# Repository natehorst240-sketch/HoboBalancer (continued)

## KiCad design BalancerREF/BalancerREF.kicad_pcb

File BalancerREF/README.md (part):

# BalancerREF (HOBOVibe) — reference rotor-vibration puck

ESP32-S3 firmware is in [firmware/README.md](firmware/README.md), including build/flash instructions, MR-VERT/TR-VERT controls, BLE/USB protocol, and a MicroVib comparison logger. Its measurement accuracy remains subject to bench validation.

Open **BalancerREF.kicad_pro**, then **BalancerREF.kicad_sch**, in KiCad 10.0.3 or later (KiCad 10 format; KiCad 9 will not open it). One A2 schematic sheet, Rev G (2026-09-19), hand-laid-out in KiCad (title "HOBOVibe Hobby Helicopter Dynamic Balancer"). The PCB is 50 x 50 mm, four layers (In1 GND plane, In2 +3V3 plane), fully routed with both inner planes uncut (the power nets that had crossed the +3V3 plane were moved to the outer layers on 2026-09-18). The custom library and project library table travel with the schematic. Most symbols are standard KiCad 10 symbols; IIS3DWB, SN74LVC1G123, LM1815, TS3021 and BQ24075RGT have local definitions with pin mappings verified against the manufacturer tables (see DATASHEET-VERIFICATION.md). The embedded USB-C receptacle and potentiometer symbols were re-synced from the KiCad 10 library (`scripts/sync_kicad10_symbols.py`) because KiCad 10 renamed the USB-C shield pin and footprint pad from S1 to SH; the pre-sync project is archived in `archives/RevB-before-kicad10-symbol-sync-20260907-214948.zip`.

This is a reference/troubleshooting instrument for approximate RPM, 1/rev vibration magnitude, phase, stability and trends. Maintenance balancing remains with calibrated MicroVib/DynaVibe equipment. Firmware and physical performance have not been validated by schematic ERC.

## Review files

- `review/BalancerREF.pdf`: searchable vector rendering of the one-sheet schematic.
- `review/erc.rpt`: KiCad 10 ERC report, all severities included.
- `review/connectivity-check.txt`: independent exact-net comparison against the intended circuits.
- `review/IC-pin-audit.csv`: every IC physical pad, manufacturer function, resulting net and unused-pin explanation.
- `review/pin-net-connections.csv`: all component pin/net connections.
- `review/unused-pins.json`: reasons for every NC marker.
- `DATASHEET-VERIFICATION.md`: manufacturer sources, pinout decisions and calculations.

All local functional circuits use real wires. Labels carry signals between complete blocks. Test points stay beside their measured circuits. Ground symbols all represent the same common ground.

## Operating intent

| Profile | Tach input | IR emitter | Vibration |
|---|---|---|---|
| MR-VERT | External isolated two-wire VR pickup at J3 / J_MAG | Off | Internal IIS3DWB on SPI, all axes available |
| TR-VERT | Onboard pulsed-red synchronous-detection optical tach (retroreflective tape) | 20 kHz pulses | Same sensor |

### Rev G changes (2026-09-19)

Three corrections from a Reddit review of the Rev C sheet, all of which still applied
to Rev F. `scripts/rev_g_usb_esd_tvs_u9.py` edits the schematic and
`scripts/sync_board_rev_g.py` carries the result into the board.

- **D3 was backwards.** The SMF5.0A is a unidirectional TVS, and DATASHEET-VERIFICATION.md
  had recorded it as bidirectional with "either orientation valid". It was drawn cathode
  to GND, anode to VBUS: forward biased, so it would have clamped USB VBUS at a diode
  drop as soon as a cable went in. Cathode (pin 1) is now on USB_VBUS and the board
  footprint is rotated 180 to match.
- **USB data lines now go through U7.** The SRV05-4's pins 4 and 6 were marked NC, so
  D+/D- reached the array as stubs. Pin 6 is directly across from pin 1 and pin 4 across
  from pin 3, so the drawing now takes D- in at pin 1 and out at pin 6, D+ in at pin 3
  and out at pin 4, and the pads on the board carry those nets. The SRV05-4 has no
  internal path between its I/O pins, so both ends of each pair keep the same net name
  and the trace itself makes the through-connection: `scripts/route_rev_g.py` runs a
  0.2 mm track straight across the package from pin 3 to pin 4 and from pin 1 to pin 6.
- **U9 pin 1 no longer floats when the head is unplugged.** OPT_COMP arrives from the
  optical head through J5 pin 5 (driven via R32 on the head). In MR-VERT the head is
  normally not connected, leaving a CMOS input open. R39 100k to GND holds it low; it is
  placed on the back directly under the OPT_COMP trace just left of U9, so one via at each
  pad connects it. U9 pin 2 (via R29 from OPT_LED_EN) floats
  only during ESP32 reset, when the GPIO is still an input, and was left alone.
- `review/reddit/` re-rendered from the Rev G sheet at higher resolution (the old set
  was Rev C at roughly 200 DPI; see `scripts/render_review_images.py`).

### Rev F changes (2026-09-13)

Rev F is the **repo-review revision**: no new function, but several things that had to
be right before any copper is routed. Every claim was checked against the manufacturer
source, and two of them did not survive that check (see DATASHEET-VERIFICATION.md for
the full record, including what was deliberately NOT changed).

- **PD1 polarity corrected - the optical tach could never have worked.** The detector
  was wired cathode to +3V3 and anode to the transimpedance summing node. Reverse bias
  is correct that way, which is why it survived this long, but photocurrent leaves the
  ANODE, so it was injected into the summing node instead of pulled out of it. The
  inverting TIA then drove TIA_OUT down, the inverting second stage drove OPT_AMP UP
  from its 1.65 V idle, and U4 has OPT_AMP on IN- against a 1.016 V threshold on IN+.
  The comparator input sat 634 mV above the threshold and light pushed it further away,
  so the output never left its low state and TR-VERT had no tach at all. Cathode now
  goes to PD_TIA_IN and the anode to GND: same 1.65 V reverse bias, but TIA_OUT rises,
  OPT_AMP falls through the threshold, and the 470k hysteresis works as drawn. About
  5.3 uA of photocurrent trips it. Bonus: the emitter turn-off edge, which lands inside
  the gate window and cannot be rejected, now couples into the summing node in the
  non-detection direction - which matters because this revision also moved Q1 nearer
  PD1.
- **R18 3.0 -> 3.9 ohm on the head board.** The emitter runs from SYS_SW, and the
  BQ24075 regulates OUT to 5.5 V, so the old value gave about 1.1 A peak into D1's 1 A
  absolute maximum. The BOM note had only checked the 4.2 V battery case. This is a
  regression introduced by Rev E: the Schottky it removed had been holding SYS near
  4.55 V. 3.9 ohm keeps the 500 mA design point at a full cell and lands at about
  0.90 A worst case.
- **U9 SN74LVC1G08 -> SN74LVC1G132.** R29/C26 fed the AND gate a 0.47 us edge against a
  10 ns/V input transition spec. The 1G132 is a Schmitt NAND on the identical SOT-23-5
  pinout, so the footprint is untouched, and it conditions both inputs rather than only
  the RC branch. It inverts, so U10's trigger moved from B rising to ~A falling - the
  SN74LVC1G123 supports both edges.
- **Switching loop off the vias.** L1 and C4-C7 were on the back with U6 on the front,
  so a 2.4 MHz switching node and both its input and output caps reached the IC through
  vias. They moved to U6's face, and C1/C2/C3/C30 followed for the BQ24075. The
  "ICs front, passives back" rule does not survive contact with a switching converter.
  Two follow-on corrections came out of review: aim at the **pin**, not the net, and
  place the fastest part first. U6 pins 5-8 are all on SYS_SW, so targeting "the input
  net" had put the caps next to EN and PS/SYNC - logic inputs that happen to be strapped
  high - rather than VIN and VINA; and the 10u bulk had taken the close spot while the
  100n sat 4.4 mm out. C5 now sits 2.07 mm from VINA and C4 2.68 mm from VIN. C1, the
  100n bypass on the BQ24075's IN pin, turned out to be **24 mm away on the back of the
  board**, which is the same as not fitting it; it is now 5.3 mm out on the front.
  TP6 and TP10 were squatting immediately left of U6 - the side VIN and PGND are on -
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
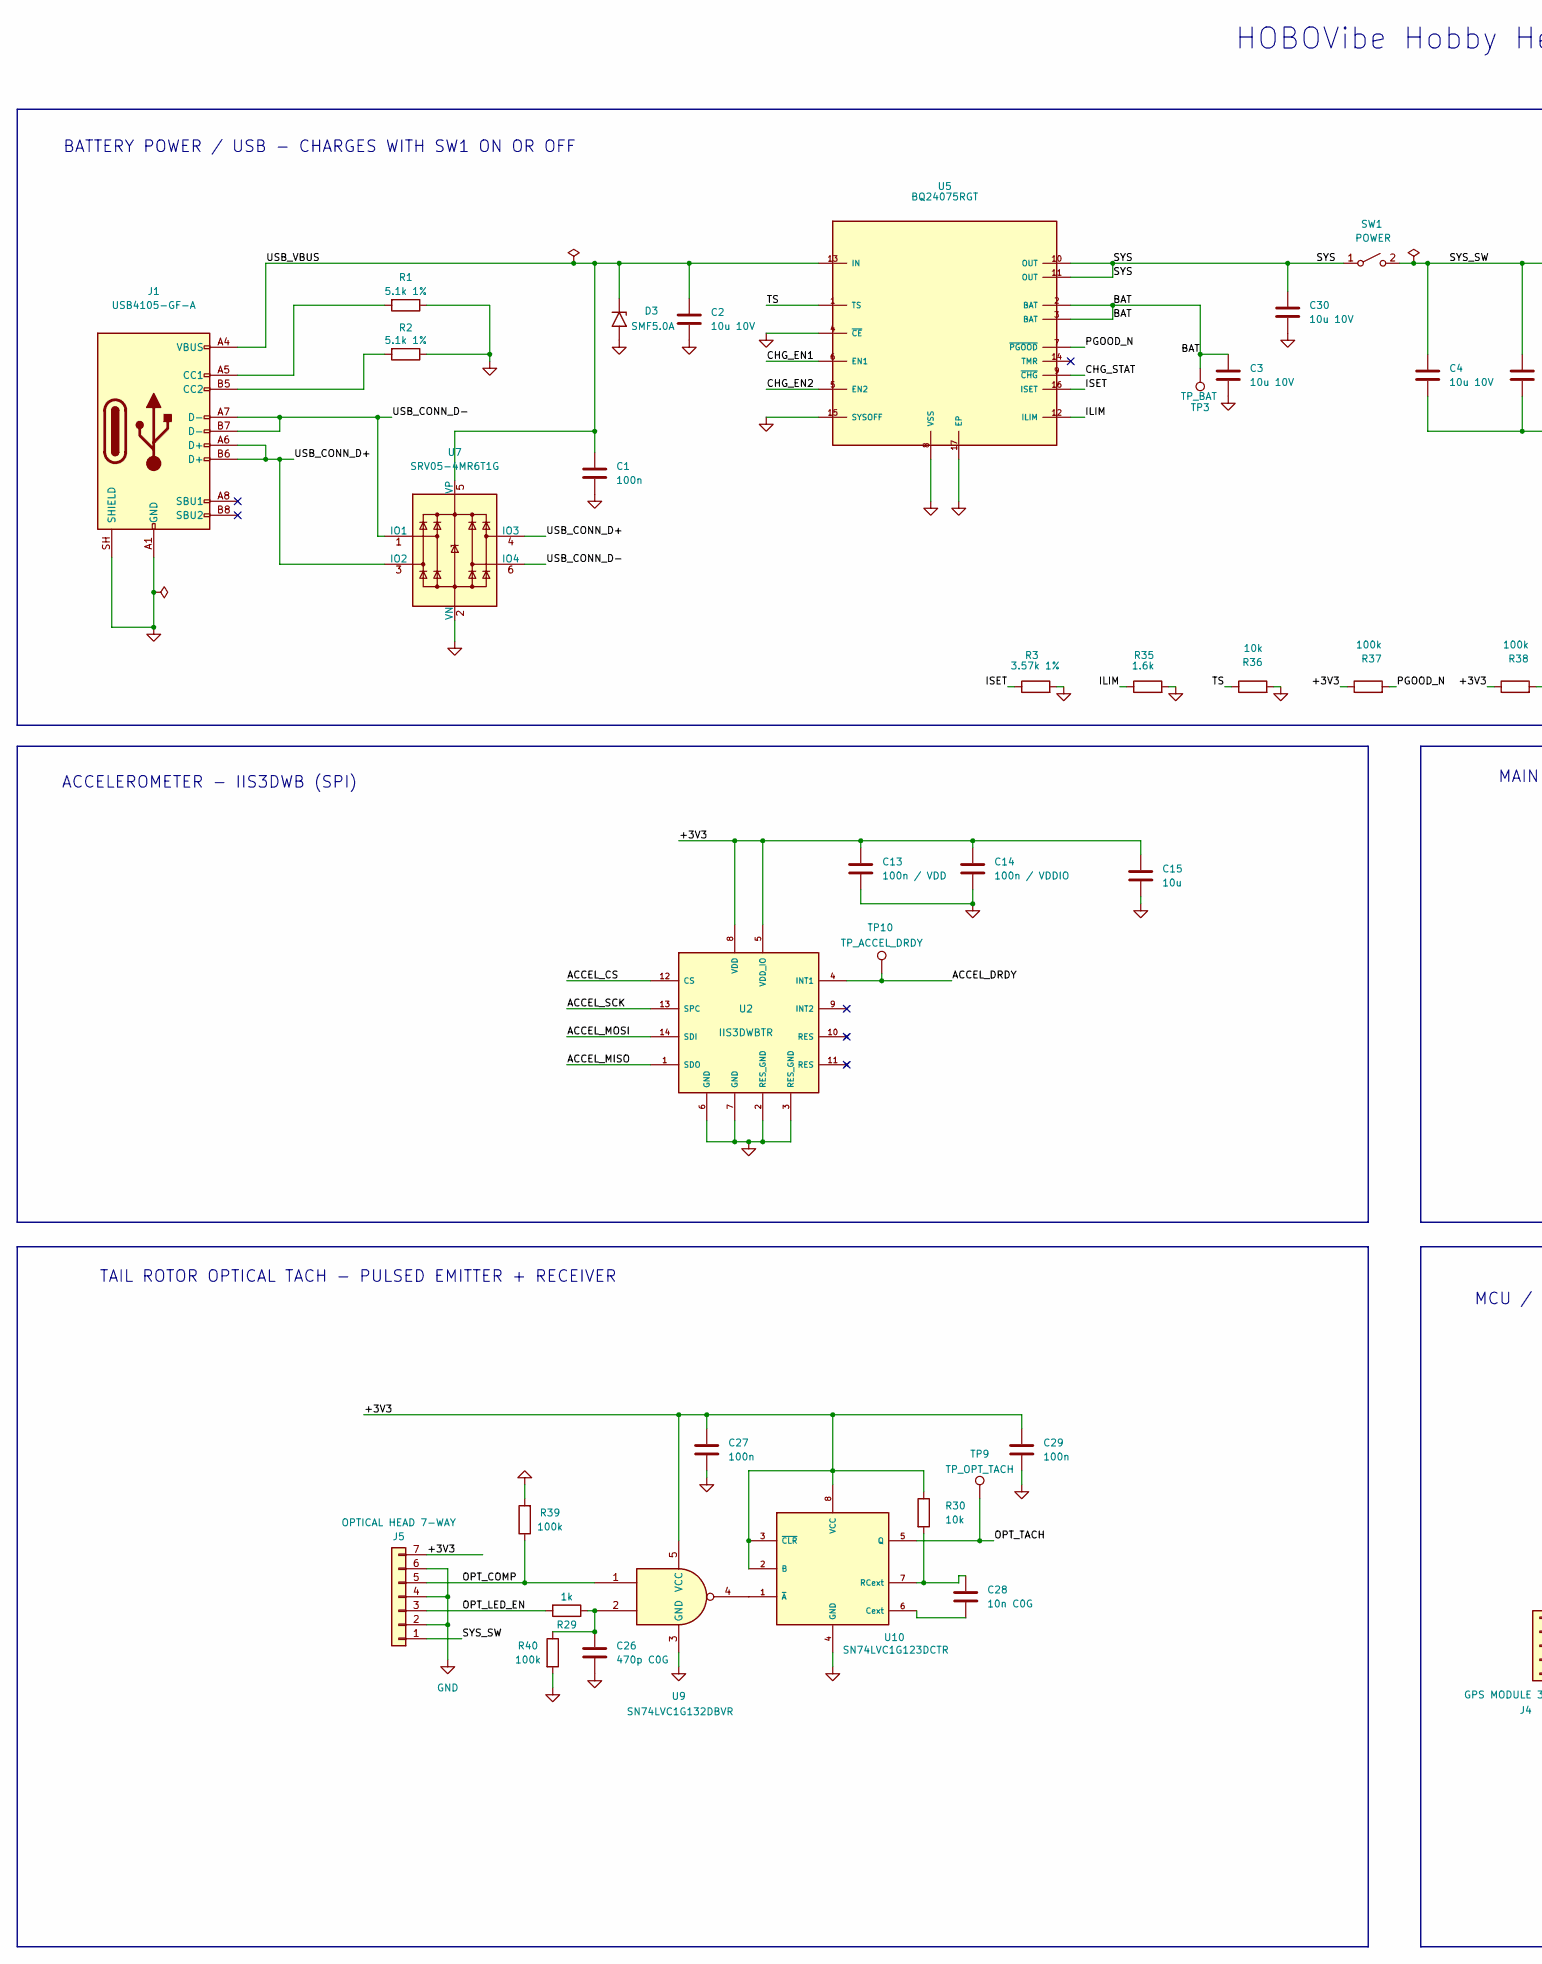
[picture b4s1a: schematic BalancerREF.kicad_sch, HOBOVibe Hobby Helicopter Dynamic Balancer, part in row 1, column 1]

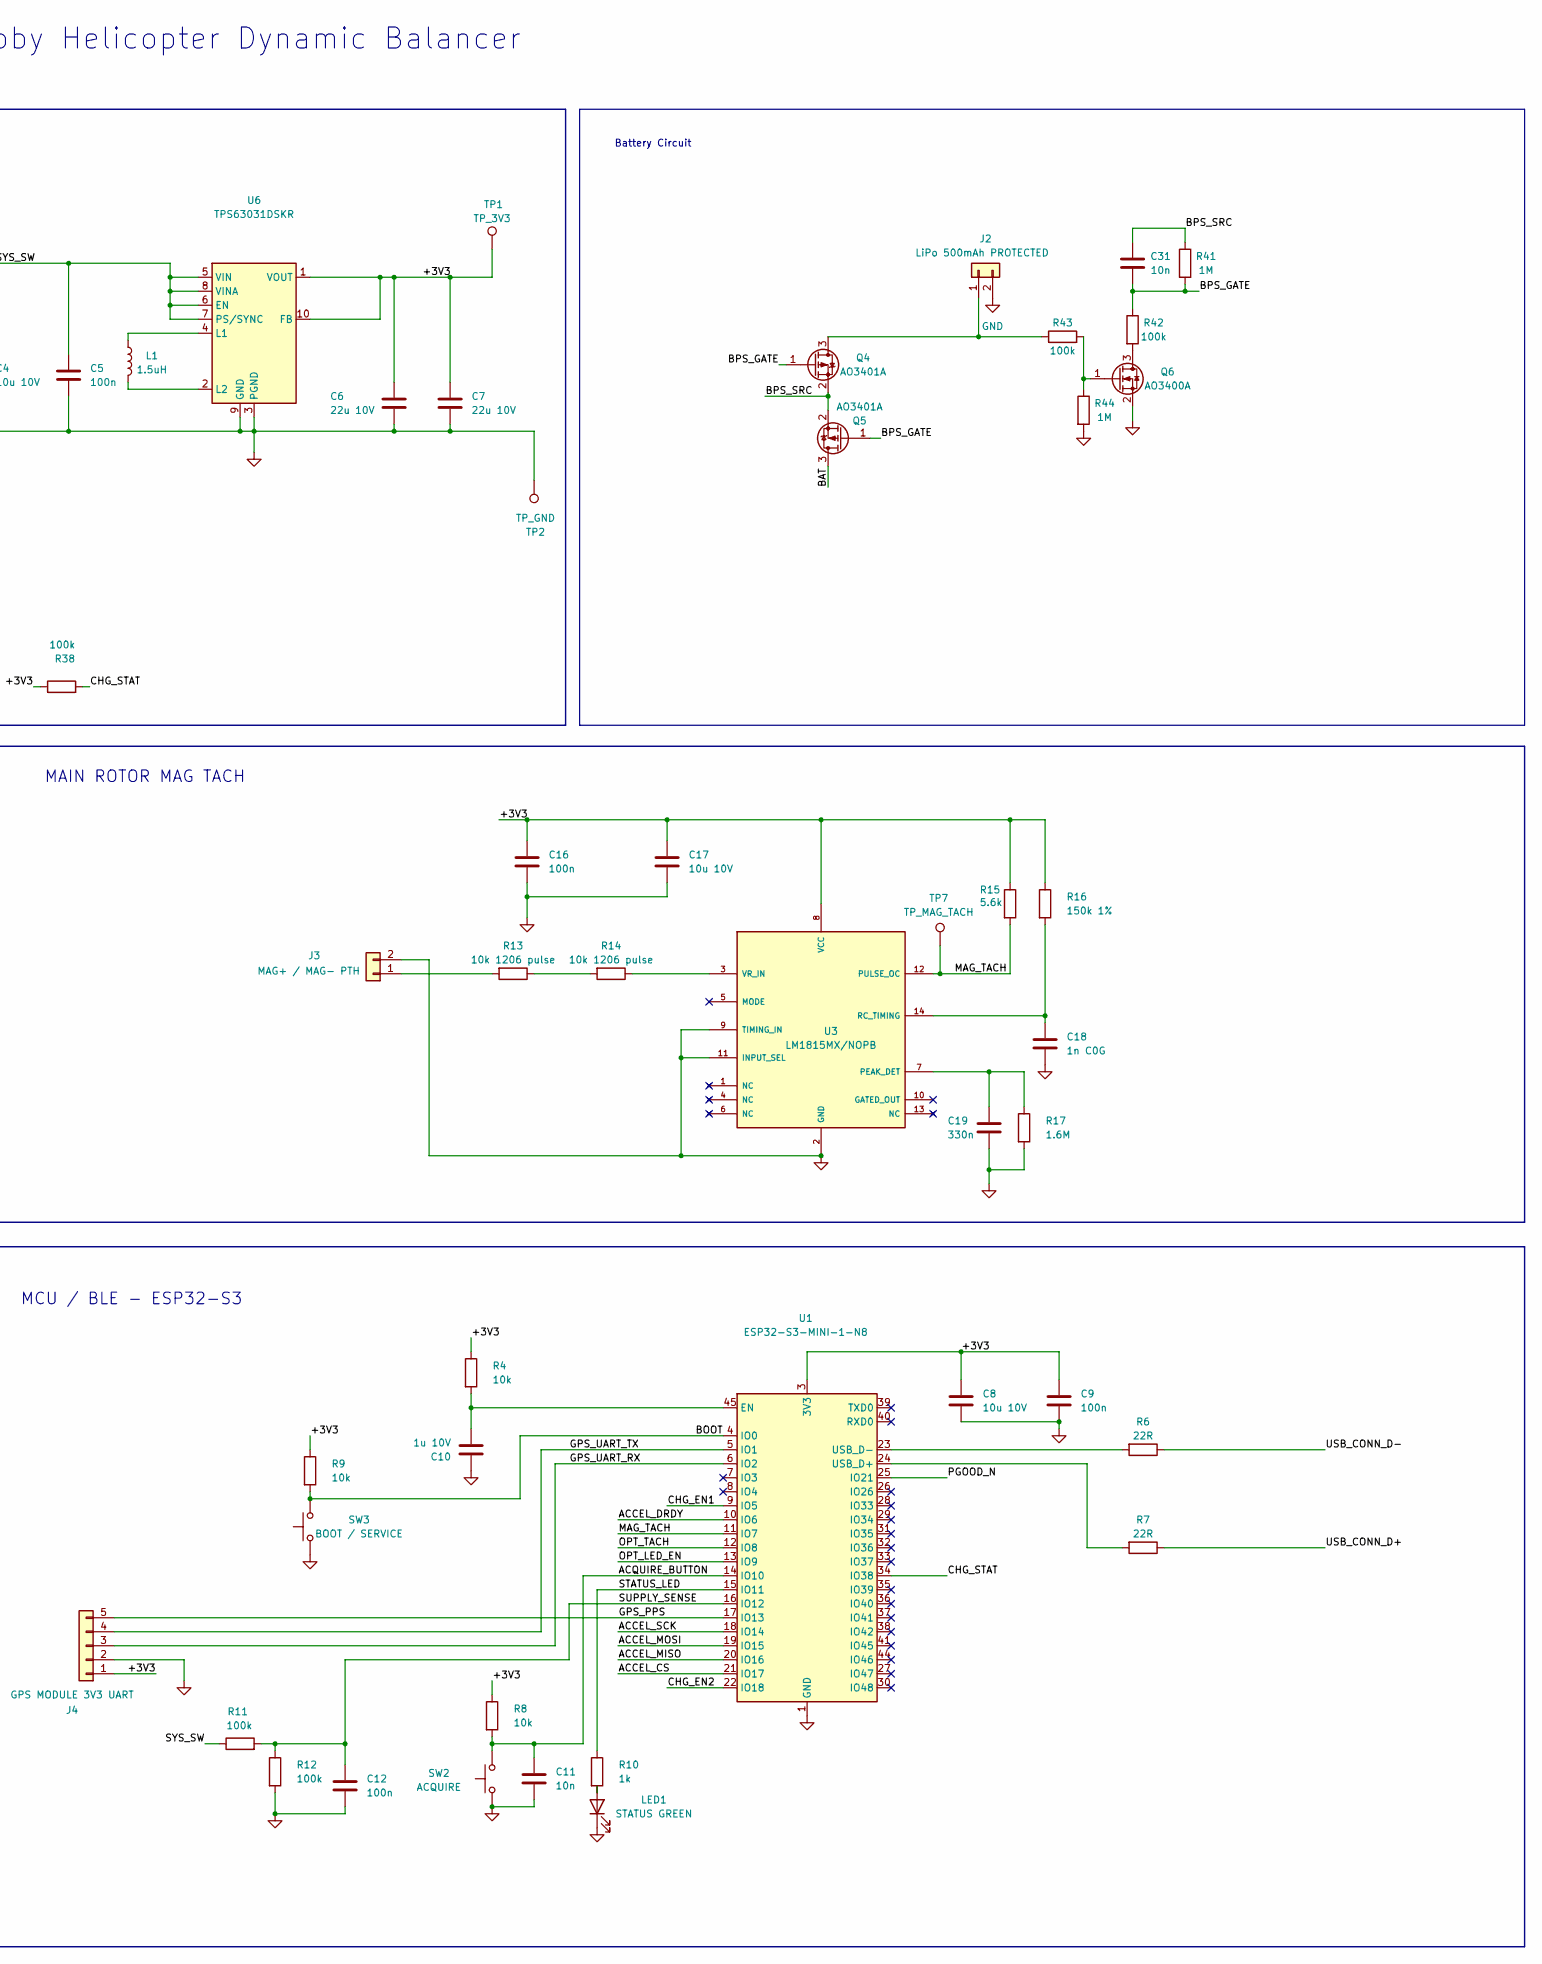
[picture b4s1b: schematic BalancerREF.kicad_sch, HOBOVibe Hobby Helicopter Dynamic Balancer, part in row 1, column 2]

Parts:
C1, C5, C9: 100n; C_0805_2012Metric; MPN 100n / 10V
C2, C3, C4, C8: 10u 10V; C_0805_2012Metric; MPN 10u / 10V X7R
C6, C7: 22u 10V; C_0805_2012Metric; MPN 22u / 10V X7R
C10: 1u 10V; C_0805_2012Metric; MPN 1u / 10V
C11, C31: 10n; C_0805_2012Metric; MPN 10n
C12, C16, C27, C29: 100n; C_0805_2012Metric; MPN 100n
C13: 100n / VDD; C_0805_2012Metric; MPN 100n / VDD
C14: 100n / VDDIO; C_0805_2012Metric; MPN 100n / VDDIO
C15: 10u; C_0805_2012Metric; MPN 10u
C17: 10u 10V; C_0805_2012Metric; MPN 10u / 10V
C18: 1n C0G; C_0805_2012Metric; MPN 1n C0G
C19: 330n; C_0805_2012Metric; MPN 330n
C26: 470p C0G; C_0805_2012Metric; MPN 470p C0G
C28: 10n C0G; C_0805_2012Metric; MPN 1n C0G
C30: 10u 10V; C_0805_2012Metric; MPN 10u 10V
D3: SMF5.0A; D_SMF; MPN SMF5.0A
J1: USB4105-GF-A; USB_C_Receptacle_GCT_USB4105-xx-A_16P_TopMnt_Horizontal; MPN USB4105-GF-A
J2: LiPo 500mAh PROTECTED; JST_PH_B2B-PH-K_1x02_P2.00mm_Vertical; MPN JST B2B-PH-K-S
J3: MAG+ / MAG- PTH; SolderWire-0.1sqmm_1x02_P3.6mm_D0.4mm_OD1mm; MPN MAG+ / MAG- PTH
J4: GPS MODULE 3V3 UART; PinHeader_1x05_P2.54mm_Vertical; MPN PinHeader 1x05 2.54mm
J5: OPTICAL HEAD 7-WAY; JST_GH_SM07B-GHS-TB_1x07-1MP_P1.25mm_Horizontal; MPN SM07B-GHS-TB
L1: 1.5uH; L_Murata_DFE201610P; MPN DFE201612PD-1R5M=P2
LED1: STATUS GREEN; LED_0603_1608Metric; MPN STATUS GREEN
Q4, Q5: AO3401A; SOT-23; MPN AO3401A
Q6: AO3400A; SOT-23; MPN AO3400A
R1, R2: 5.1k 1%; R_0603_1608Metric; MPN 5.1k 1%
R3: 3.57k 1%; R_0603_1608Metric; MPN 3.57k 1%
R4, R8, R9, R36: 10k; R_0603_1608Metric; MPN 10k
R6, R7: 22R; R_0603_1608Metric; MPN 22R
R10, R29: 1k; R_0603_1608Metric; MPN 1k
R11, R12, R37, R38, R39, R40, R42, R43: 100k; R_0603_1608Metric; MPN 100k
R13, R14: 10k 1206 pulse; R_1206_3216Metric; MPN 10k 1206 pulse
R15: 5.6k; R_0603_1608Metric; MPN 5.6k
R16: 150k 1%; R_0603_1608Metric; MPN 150k 1%
R17: 1.6M; R_0603_1608Metric; MPN 1.6M
R30: 10k; R_0603_1608Metric; MPN 100k
R35: 1.6k; R_0603_1608Metric; MPN 1.6k
R41, R44: 1M; R_0603_1608Metric; MPN 1M
SW1: POWER; SW_Slide-03_Wuerth-WS-SLTV_10x2.5x6.4_P2.54mm; MPN POWER
SW2: ACQUIRE; SW_PUSH_6mm; MPN ACQUIRE
SW3: BOOT / SERVICE; SW_PUSH_6mm; MPN BOOT / SERVICE
TP1: TP_3V3; TestPoint_Pad_D1.0mm; MPN TP_3V3
TP2: TP_GND; TestPoint_Pad_D1.0mm; MPN TP_GND
TP3: TP_BAT; TestPoint_Pad_D1.0mm; MPN TP_BAT
TP7: TP_MAG_TACH; TestPoint_Pad_D1.0mm; MPN TP_MAG_TACH
TP9: TP_OPT_TACH; TestPoint_Pad_D1.0mm; MPN TP_OPT_TACH
TP10: TP_ACCEL_DRDY; TestPoint_Pad_D1.0mm; MPN TP_ACCEL_DRDY
U1: ESP32-S3-MINI-1-N8; ESP32-S2-MINI-1; MPN ESP32-S3-MINI-1-N8
U2: IIS3DWBTR; LGA-14_3x2.5mm_P0.5mm_LayoutBorder3x4y; MPN IIS3DWBTR
U3: LM1815MX/NOPB; SOIC-14_3.9x8.7mm_P1.27mm; MPN LM1815MX/NOPB
U5: BQ24075RGT; QFN-16-1EP_3x3mm_P0.5mm_EP1.675x1.675mm; MPN BQ24075RGTR
U6: TPS63031DSKR; WSON-10-1EP_2.5x2.5mm_P0.5mm_EP1.2x2mm; MPN TPS63031DSKR
U7: SRV05-4MR6T1G; SOT-23-6; MPN SRV05-4MR6T1G
U9: SN74LVC1G132DBVR; SOT-23-5; MPN SN74LVC1G132DBVR
U10: SN74LVC1G123DCTR; SSOP-8_2.95x2.8mm_P0.65mm; MPN SN74LVC1G123DCTR

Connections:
/+3V3: C6.1, C7.1, C8.1, C9.1, C13.1, C14.1, C15.1, C16.1, C17.1, C27.1, C29.1, J4.1, J5.7, R4.1, R8.1, R9.1, R15.1, R16.1, R30.1, R37.1, R38.1, TP1.1 (1_1), U1.3 (3V3), U2.5 (VDD_IO), U2.8 (VDD), U3.8 (VCC), U6.1 (VOUT), U6.10 (FB), U9.5 (VCC), U10.2 (B), U10.3 (~CLR), U10.8 (VCC)
/ACCEL_CS: U1.21 (IO17), U2.12 (CS)
/ACCEL_DRDY: TP10.1 (1_1), U1.10 (IO6), U2.4 (INT1)
/ACCEL_MISO: U1.20 (IO16), U2.1 (SDO)
/ACCEL_MOSI: U1.19 (IO15), U2.14 (SDI)
/ACCEL_SCK: U1.18 (IO14), U2.13 (SPC)
/ACQUIRE_BUTTON: C11.1, R8.2, SW2.2, U1.14 (IO10)
/BAT: C3.1, Q5.3 (D), TP3.1 (1_1), U5.2 (BAT), U5.3 (BAT)
/BOOT: R9.2, SW3.2, U1.4 (IO0)
/BPS_GATE: C31.2, Q4.1 (G), Q5.1 (G), R41.2, R42.1
/BPS_SRC: C31.1, Q4.2 (S), Q5.2 (S), R41.1
/CHG_EN1: U1.9 (IO5), U5.6 (EN1)
/CHG_EN2: U1.22 (IO18), U5.5 (EN2)
/CHG_STAT: R38.2, U1.34 (IO38), U5.9 (~CHG)
/GPS_PPS: J4.5, U1.17 (IO13)
/GPS_UART_RX: J4.3, U1.6 (IO2)
/GPS_UART_TX: J4.4, U1.5 (IO1)
/ILIM: R35.1, U5.12 (ILIM)
/ISET: R3.1, U5.16 (ISET)
/MAG_TACH: R15.2, TP7.1 (1_1), U1.11 (IO7), U3.12 (PULSE_OC)
/OPT_COMP: J5.5, R39.1, U9.1
/OPT_LED_EN: J5.3, R29.2, U1.13 (IO9)
/OPT_TACH: TP9.1 (1_1), U1.12 (IO8), U10.5 (Q)
/PGOOD_N: R37.2, U1.25 (IO21), U5.7 (~PGOOD)
/STATUS_LED: R10.1, U1.15 (IO11)
/SUPPLY_SENSE: C12.1, R11.2, R12.1, U1.16 (IO12)
/SYS: C30.1, SW1.1 (A), U5.10 (OUT), U5.11 (OUT)
/SYS_SW: C4.1, C5.1, J5.1, R11.1, SW1.2 (B), U6.5 (VIN), U6.6 (EN), U6.7 (PS/SYNC), U6.8 (VINA)
/TS: R36.1, U5.1 (TS)
/USB_CONN_D+: J1.A6 (D+), J1.B6 (D+), R7.1, U7.3 (IO2), U7.4 (IO3)
/USB_CONN_D-: J1.A7 (D-), J1.B7 (D-), R6.1, U7.1 (IO1), U7.6 (IO4)
/USB_VBUS: C1.1, C2.1, D3.1 (A1), J1.A4 (VBUS), J1.A9 (VBUS), J1.B4 (VBUS), J1.B9 (VBUS), U5.13 (IN), U7.5 (VP)
GND: C1.2, C2.2, C3.2, C4.2, C5.2, C6.2, C7.2, C8.2, C9.2, C10.2, C11.2, C12.2, C13.2, C14.2, C15.2, C16.2, C17.2, C18.2, C19.2, C26.2, C27.2, C29.2, C30.2, D3.2 (A2), J1.A1 (GND), J1.A12 (GND), J1.B1 (GND), J1.B12 (GND), J1.SH (SHIELD), J2.2, J3.2, J4.2, J5.2, J5.4, J5.6, LED1.1 (K), Q6.2 (S), R1.1, R2.1, R3.2, R12.2, R17.2, R35.2, R36.2, R39.2, R40.2, R44.2, SW2.1, SW3.1, TP2.1 (1_1), U1.1 (GND), U1.2 (GND), U1.42 (GND), U1.43 (GND), U1.46 (GND), U1.47 (GND), U1.48 (GND), U1.49 (GND), U1.50 (GND), U1.51 (GND), U1.52 (GND), U1.53 (GND), U1.54 (GND), U1.55 (GND), U1.56 (GND), U1.57 (GND), U1.58 (GND), U1.59 (GND), U1.60 (GND), U1.61 (GND), U1.62 (GND), U1.63 (GND), U1.64 (GND), U1.65 (GND), U2.2 (RES_GND), U2.3 (RES_GND), U2.6 (GND), U2.7 (GND), U3.2 (GND), U3.9 (TIMING_IN)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
unnamed: C26.1, R29.1, R40.1, U9.2
unnamed: J1.A5 (CC1), R1.2
unnamed: J1.B5 (CC2), R2.2
unnamed: J2.1, Q4.3 (D), R43.1
unnamed: J3.1, R13.2
unnamed: LED1.2 (A), R10.2
unnamed: Q6.3 (D), R42.2
unnamed: Q6.1 (G), R43.2, R44.1
unnamed: R13.1, R14.2
unnamed: C10.1, R4.2, U1.45 (EN)
unnamed: R7.2, U1.24 (USB_D+)
unnamed: R6.2, U1.23 (USB_D-)
unnamed: C19.1, R17.1, U3.7 (PEAK_DET)
unnamed: C18.1, R16.2, U3.14 (RC_TIMING)
unnamed: R14.1, U3.3 (VR_IN)
unnamed: L1.1, U6.4 (L1)
unnamed: L1.2, U6.2 (L2)
unnamed: C28.2, U10.6 (Cext)
unnamed: C28.1, R30.2, U10.7 (RCext)
unnamed: U9.4, U10.1 (~A)

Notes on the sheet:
Battery Circuit
BATTERY POWER / USB - CHARGES WITH SW1 ON OR OFF
MCU / BLE - ESP32-S3
HOBOVibe Hobby Helicopter Dynamic Balancer
ACCELEROMETER - IIS3DWB (SPI)
MAIN ROTOR MAG TACH
TAIL ROTOR OPTICAL TACH - PULSED EMITTER + RECEIVER

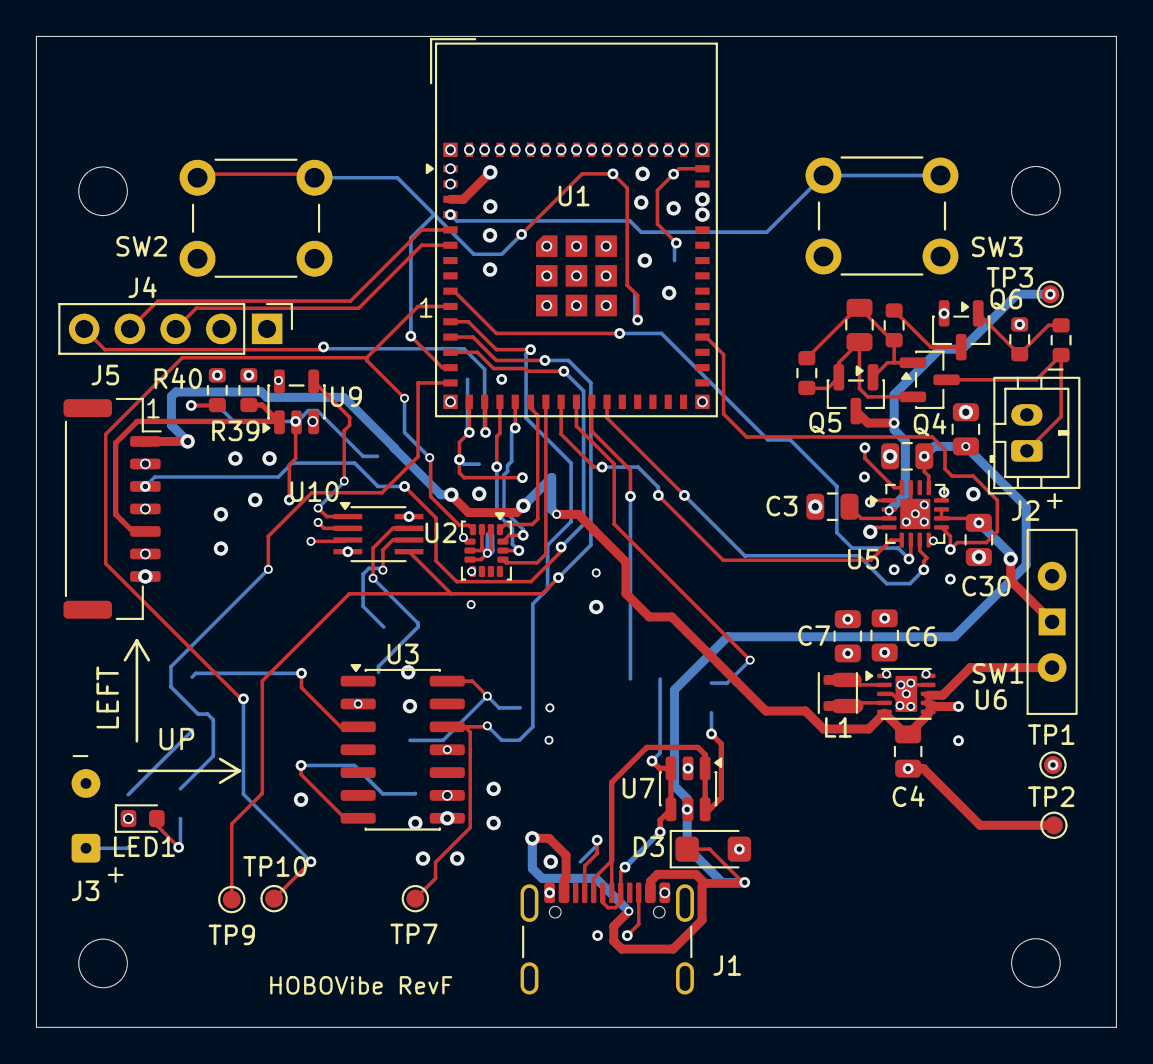
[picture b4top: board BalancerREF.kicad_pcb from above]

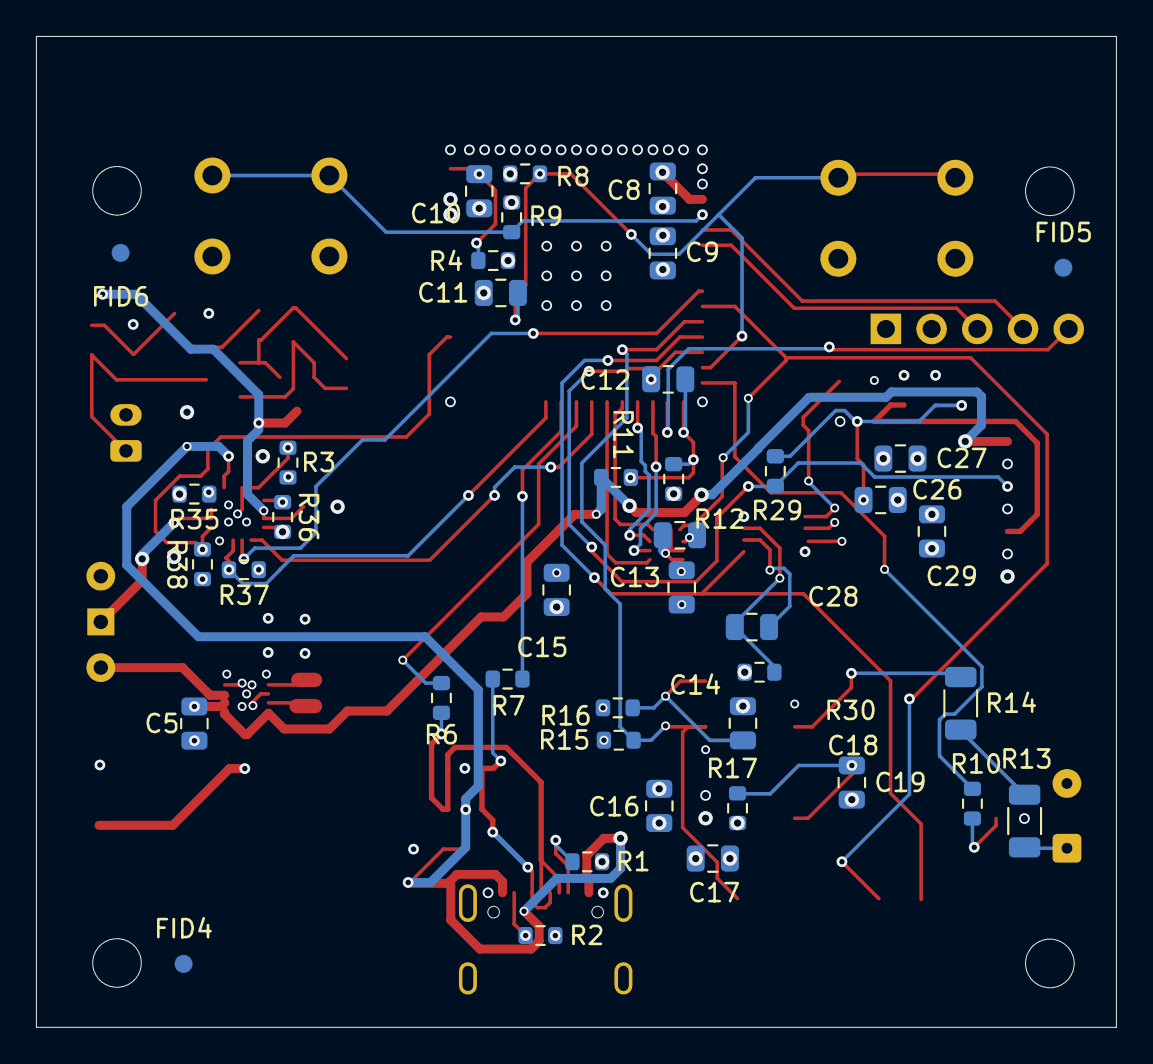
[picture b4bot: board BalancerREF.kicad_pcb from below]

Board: 4 copper layers, 60.0 x 55.0 mm, 88 parts (42 on the bottom side), 53 nets.

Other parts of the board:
FID4, FID5, FID6: FIDUCIAL; Fiducial_1mm_Mask2mm
H1, H2, H3, H4: M2.5 MOUNT; MountingHole_2.7mm_M2.5

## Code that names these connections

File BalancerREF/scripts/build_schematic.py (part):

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 rr=R('22R',368.3,yy,90);wire((358.14,yy),p(rr,2));route(rr,1,(401.32,yy));label(net,401.32,yy)
 tp(tpref,'TP_USB_D-' if n==23 else 'TP_USB_D+',388.62,yy-5.08,(388.62,yy))
# GPIO allocations deliberately avoid strapping pins and internal flash signals.
gpio={10:'ACCEL_DRDY',11:'MAG_TACH',12:'OPT_TACH',13:'OPT_LED_EN',14:'ACQUIRE_BUTTON',15:'STATUS_LED',16:'SUPPLY_SENSE',18:'ACCEL_SCK',19:'ACCEL_MOSI',20:'ACCEL_MISO',21:'ACCEL_CS'}
for pin,net in gpio.items():
 a=p('U1',pin);wire(a,(241.3,a[1]));label(net,241.3,a[1])
usedpins={3,45,4,23,24,*gpio.keys(),1,2,42,43,*range(46,66)}
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 wire((x,182.88),(x+20.32,182.88));label(net,x+20.32,182.88)
 if ref=='SW2':
  cc=C('10n',60.96,195.58);route(cc,1,(60.96,182.88));route(cc,2,(60.96,208.28),(40.64,208.28))
rs=R('1k',139.7,170.18);route(rs,1,(139.7,160.02));label('STATUS_LED',139.7,160.02)
place('LED1',('Device','LED'),139.7,190.5,90,'STATUS GREEN',fp='LED_SMD:LED_0603_1608Metric',field=(150,189.23));route(rs,2,p('LED1',2));route('LED1',1,(139.7,208.28));gnd(139.7,208.28)
# Switched supply divider: cannot back-power the MCU when SW1 is OFF.
rh=R('100k',35.56,233.68);rl=R('100k',68.58,241.3)
route(rh,1,(35.56,223.52));rail('SYS_SW',35.56,223.52)
route(rh,2,(35.56,236.22),(68.58,236.22),p(rl,1));route(rl,2,(68.58,251.46));gnd(68.58,251.46)
wire((68.58,236.22),(91.44,236.22));label('SUPPLY_SENSE',91.44,236.22)
ca=C('100n',81.28,243.84);route(ca,1,(81.28,236.22));route(ca,2,(81.28,251.46),(68.58,251.46))
text('Active-low buttons; debounce in firmware.\nBOOT held low during reset enters download.\nSupply ADC: SYS_SW / 2 with 100n at the pin; dead when OFF.\nOne green status LED; patterns set by firmware.',101.6,220.98,1.2)

# Accelerometer: IIS3DWB on 4-wire SPI. RES pads 2/3 to GND, 10/11 unconnected, INT1 = data-ready.
place('U2','IIS3DWBTR',99.06,325.12,field=(99.06,302.26),mpn='IIS3DWBTR')
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 a=p('U2',n);wire(a,(20.32,a[1]));label(net,20.32,a[1],180)
for n in [6,7,2,3]:route('U2',n,(p('U2',n)[0],350.52))
wire((91.44,350.52),(106.68,350.52));gnd(99.06,350.52)
route('U2',4,(151.13,317.5));label('ACCEL_DRDY',151.13,317.5)
tp('TP10','TP_ACCEL_DRDY',124.46,312.42,(124.46,317.5))
nc('U2',9,'INT2 unused');nc('U2',10,'Reserved pad: leave unconnected per ST DS12569');nc('U2',11,'Reserved pad: leave unconnected per ST DS12569')
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for n in [1,4,6,13]:nc('U3',n,'No internal connection per TI')
nc('U3',10,'Unused gated output; using open-collector reference pulse on pin 12')
ro=R('5.6k',365.76,307.34);route(ro,1,(365.76,292.1));route(ro,2,(365.76,320.04))
route('U3',12,(365.76,320.04));label('MAG_TACH',365.76,320.04)
tp('TP7','TP_MAG_TACH',353.06,314.96,(353.06,320.04))
rt=R('150k 1%',325.12,307.34);route(rt,1,(325.12,292.1));route(rt,2,(325.12,327.66),p('U3',14))
ct=C('1n C0G',325.12,340.36);route(ct,1,(325.12,327.66));route(ct,2,(325.12,358.14));gnd(325.12,358.14)
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 if getprop(inst,'Reference')==cbk:next(z for z in children(inst,'property') if z[1]=='Footprint')[2]='Capacitor_SMD:C_1210_3225Metric'
place('D1',('Device','LED'),406.4,317.5,90,'XPEBRD-L1 625nm',fp='LED_SMD:LED_Cree-XP',field=(414.02,312.42),mpn='XPEBRD-L1-0000-00501');route(re,2,p('D1',2))
place('Q1',('Transistor_FET','AO3400A'),403.86,337.82,value='AO3400A',field=(414.02,332.74));route('D1',1,p('Q1',3));route('Q1',2,(406.4,363.22));gnd(406.4,363.22)
rg=R('100R',398.78,353.06,90);route(rg,1,(421.64,353.06),(421.64,347.98),(393.7,347.98),(393.7,337.82),p('Q1',1));route(rg,2,(391.16,353.06));label('OPT_LED_EN',391.16,353.06,180)
rpd=R('100k',421.64,358.14);route(rpd,1,(421.64,347.98));route(rpd,2,(421.64,363.22),(406.4,363.22))
# Receiver: BPW34S reverse-biased into a 10k transimpedance stage referenced to 1.65 V, then x12 inverting AC gain.
wire((434.34,292.1),(571.5,292.1));rail('+3V3',434.34,292.1)
place('PD1',('Sensor_Optical','BPW34'),441.96,320.04,270,'BPW34S',fp='OptoDevice:Osram_BPW34S-SMD',field=(444.5,325.12),mpn='BPW34S')
route('PD1',1,(441.96,292.1));route('PD1',2,(472.44,322.58))
place('U8',('Amplifier_Operational','TLV9062xD'),480.06,320.04,value='TLV9062IDR',fp='Package_SO:SOIC-8_3.9x4.9mm_P1.27mm',field=(477.52,330.2),mpn='TLV9062IDR',unit=1)
wire((472.44,317.5),(459.74,317.5));label('OPT_VREF',459.74,317.5)
rf=R('10k',480.06,299.72,90);wire(p('U8',2),(467.36,322.58),(467.36,299.72),p(rf,2));wire(p(rf,1),(492.76,299.72),(492.76,320.04),p('U8',1))
cfb=C('10p C0G',480.06,307.34,90);wire((467.36,307.34),p(cfb,1));wire(p(cfb,2),(492.76,307.34))
# Inverting gain stage: baseline sits at VREF, received pulses swing down toward 0.45 V.
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cac=C('10n',502.92,340.36,90);rg1=R('10k',510.54,340.36,90)
wire(p(rg1,1),(516.89,340.36),(516.89,335.28))
place('U8',('Amplifier_Operational','TLV9062xD'),525.78,332.74,value='TLV9062IDR',fp='Package_SO:SOIC-8_3.9x4.9mm_P1.27mm',field=(531.11,325.12),mpn='TLV9062IDR',unit=2)
wire((516.89,335.28),p('U8',6));wire(p('U8',5),(505.46,330.2));label('OPT_VREF',505.46,330.2)
rg2=R('120k',527.05,347.98,90);route('U8',7,(538.48,332.74),(538.48,347.98),p(rg2,1));wire(p(rg2,2),(516.89,347.98),(516.89,340.36))
wire((538.48,332.74),(543.56,332.74));label('OPT_AMP',543.56,332.74)
# 1.65 V reference and op amp supply.
rb1=R('10k',548.64,302.26);rb2=R('10k',548.64,317.5)
route(rb1,1,(548.64,292.1));route(rb1,2,(548.64,309.88),p(rb2,1));route(rb2,2,(548.64,325.12));gnd(548.64,325.12)
wire((548.64,309.88),(541.02,309.88));caprail('100n',541.02,317.5,309.88,325.12);gnd(541.02,325.12);label('OPT_VREF',548.64,309.88)
place('U8',('Amplifier_Operational','TLV9062xD'),563.88,330.2,value='TLV9062IDR',fp='Package_SO:SOIC-8_3.9x4.9mm_P1.27mm',field=(569.0,326.39),mpn='TLV9062IDR',unit=3)
route('U8',8,(563.88,292.1));route('U8',4,(563.88,363.22));gnd(563.88,363.22)
cv=caprail('100n',571.5,304.8,292.1,312.42);gnd(571.5,312.42)
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# Detection row: comparator -> AND with the emitter pulse (synchronous) -> retriggerable monostable.
wire((198.12,406.4),(414.02,406.4));rail('+3V3',198.12,406.4)
place('U4','TS3021IYLT',254,431.8,field=(255.27,414.02))
wire((238.76,434.34),p('U4',4));label('OPT_AMP',238.76,434.34,180)
rth1=R('22k',233.68,416.56);rth2=R('10k',223.52,429.26,90)
route(rth1,1,(233.68,406.4));route(rth1,2,(233.68,429.26),p('U4',3));wire(p(rth2,1),(233.68,429.26));route(rth2,2,(219.71,444.5));gnd(219.71,444.5)
rhys=R('470k',256.54,452.12,90);route('U4',1,(266.7,431.8));wire((266.7,431.8),(266.7,452.12),p(rhys,1));wire(p(rhys,2),(236.22,452.12),(236.22,429.26))
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caprail('100n',274.32,416.56,406.4,424.18);gnd(274.32,424.18)
place('U9',('74xGxx','74LVC1G08'),299.72,431.8,value='SN74LVC1G08DBVR',fp='Package_TO_SOT_SMD:SOT-23-5',field=(299.72,411.48),mpn='SN74LVC1G08DBVR')
wire((266.7,431.8),(276.86,431.8),(276.86,429.26),p('U9',1))
rdly=R('1k',218.44,457.2,90);wire((203.2,457.2),p(rdly,2));label('OPT_LED_EN',203.2,457.2)
cdly=C('470p C0G',228.6,464.82);route(rdly,1,(228.6,457.2),p(cdly,1));route(cdly,2,(228.6,472.44));gnd(228.6,472.44)
wire((228.6,457.2),(279.4,457.2),(279.4,434.34),p('U9',2))
route('U9',5,(299.72,406.4));route('U9',3,(299.72,444.5));gnd(299.72,444.5)
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route('U10',4,(355.6,449.58));gnd(355.6,449.58)
rext=R('100k',381.0,421.64);route(rext,1,(381.0,414.02),(355.6,414.02));route(rext,2,(381.0,434.34));route('U10',7,(381.0,434.34))
cext=C('1n C0G',388.62,436.88);wire((381.0,434.34),(388.62,434.34),p(cext,1));route('U10',6,(388.62,439.42),p(cext,2))
route('U10',5,(398.78,426.72));label('OPT_TACH',398.78,426.72)
tp('TP9','TP_OPT_TACH',396.24,419.1,(396.24,426.72))
caprail('100n',414.02,416.56,406.4,424.18);gnd(414.02,424.18)
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text('Mechanical intent only: future PCB ~50 x 40 mm.\nNo PCB generated. Keep antenna area clear.\nRigid mount near MEMS; red acrylic optical window on LEFT.\nValidate phase delay and tach SNR on bench before use.',439.42,99.06,1.45)
text('Test points are drawn at the circuit they measure. One common GND system. NC marks only identify documented unused pins.\nBattery/USB flags denote external sources; SYS_SW flag denotes power through SW1. No flags on missing IC connections.',12.7,487.68,1.5)


# Microchip AN1149 directional power sharing: PMOS D=BAT, S=SYS.
box('USB / BATTERY POWER SHARING',431.8,137.16,147.32,121.92)
place('D2',('Device','D_Schottky'),515.62,170.18,180,'PMEG4010CEH','Diode_SMD:D_SOD-123F',field=(515.62,158.75))
wire((444.5,160.02),(487.68,160.02),(487.68,170.18),p('D2',2));label('USB_VBUS',444.5,160.02)
route('D2',1,(556.26,170.18),(556.26,200.66))
place('Q3',('Transistor_FET','AO3401A'),515.62,203.2,90,'AO3401A',field=(515.62,186.69))
wire((444.5,200.66),p('Q3',3));label('BAT',444.5,200.66)
route('Q3',2,(556.26,200.66));label('SYS',556.26,200.66)
route('Q3',1,(487.68,208.28),(487.68,160.02))
rgq=R('1k',487.68,226.06)
route(rgq,1,(487.68,208.28));route(rgq,2,(487.68,241.3));gnd(487.68,241.3)
csys=C('10u 10V',538.48,226.06)
route(csys,1,(538.48,200.66));route(csys,2,(538.48,241.3));gnd(538.48,241.3)
place('SW1',('Switch','SW_SPST'),556.26,223.52,270,'POWER',field=(568.96,216))
route('SW1',1,(556.26,200.66));route('SW1',2,(556.26,236.22),(563.88,236.22));label('SYS_SW',563.88,236.22)
text('USB supplies puck + charger; battery takes over without USB.\nSW1 switches puck only. Q3: drain=BAT, source=SYS.',439.42,248.92,1.25)
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
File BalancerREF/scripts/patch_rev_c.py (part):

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rep("node('paper','A2')", "node('paper','A1')")
rep("node('date','2026-09-07'),node('rev','B')", "node('date','2026-09-09'),node('rev','C')")
rep("(descr \"Verified symbols missing from KiCad 9\")", "(descr \"Verified local symbols\")")
rep("text('Test points are drawn at the circuit they measure. One common GND system. NC marks only identify documented unused pins.\\nBattery/USB flags denote external sources; SYS_SW flag denotes power through SW1. No flags on missing IC connections.',12.7,388.62,1.5)",
    "text('Test points are drawn at the circuit they measure. One common GND system. NC marks only identify documented unused pins.\\nBattery/USB flags denote external sources; SYS_SW flag denotes power through SW1. No flags on missing IC connections.',12.7,487.68,1.5)")

# ---------------------------------------------------------------- USB: VBUS TVS
rep("tp('TP4','TP_USB_VBUS',99.06,30.48,(99.06,35.56));flag('#FLG01',106.68,35.56);flag('#FLG02',30.48,119.38)",
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    "text('Icharge = 1000 / 4020 = 249 mA nominal. Q4 blocks a reversed pack.\\n4.2 V cell; use protected pack (no PCB cell protection).\\nCharging independent of SW1; see power sharing.\\nUSB programming: switch ON; battery optional.',139.7,111.76,1.2)")

# ---------------------------------------------------------------- user block: ADC filter
rep("wire((68.58,236.22),(91.44,236.22));label('SUPPLY_SENSE',91.44,236.22)",
    "wire((68.58,236.22),(91.44,236.22));label('SUPPLY_SENSE',91.44,236.22)\nca=C('100n',81.28,243.84);route(ca,1,(81.28,236.22));route(ca,2,(81.28,251.46),(68.58,251.46))")
rep("Supply ADC: SYS_SW / 2; dead when OFF.\\nOne green status LED",
    "Supply ADC: SYS_SW / 2 with 100n at the pin; dead when OFF.\\nOne green status LED")

# ---------------------------------------------------------------- MCU GPIO map
rep("gpio={8:'ACCEL_SDA',9:'ACCEL_SCL',10:'ACCEL_DRDY',11:'MAG_TACH',12:'OPT_TACH',13:'OPT_LED_EN',14:'ACQUIRE_BUTTON',15:'STATUS_LED',16:'SUPPLY_SENSE'}",
    "gpio={10:'ACCEL_DRDY',11:'MAG_TACH',12:'OPT_TACH',13:'OPT_LED_EN',14:'ACQUIRE_BUTTON',15:'STATUS_LED',16:'SUPPLY_SENSE',18:'ACCEL_SCK',19:'ACCEL_MOSI',20:'ACCEL_MISO',21:'ACCEL_CS'}")
rep("text('GPIO4 SDA | GPIO5 SCL | GPIO6 DRDY\\nGPIO7 MAG capture | GPIO8 OPT capture\\nGPIO9 emitter | GPIO10 acquire | GPIO11 status\\nGPIO12 supply ADC | GPIO19/20 native USB\\nMAG/OPT: GPIO matrix to MCPWM capture or RMT.',302.26,238.76,1.15)",
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 a=p('U2',n);wire(a,(20.32,a[1]));label(net,20.32,a[1],180)
for n in [6,7,2,3]:route('U2',n,(p('U2',n)[0],350.52))
wire((91.44,350.52),(106.68,350.52));gnd(99.06,350.52)
route('U2',4,(151.13,317.5));label('ACCEL_DRDY',151.13,317.5)
tp('TP10','TP_ACCEL_DRDY',124.46,312.42,(124.46,317.5))
nc('U2',9,'INT2 unused');nc('U2',10,'Reserved pad: leave unconnected per ST DS12569');nc('U2',11,'Reserved pad: leave unconnected per ST DS12569')
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 if getprop(inst,'Reference')==cbk:next(z for z in children(inst,'property') if z[1]=='Footprint')[2]='Capacitor_SMD:C_1210_3225Metric'
place('D1',('Device','LED'),406.4,317.5,90,'XPEBRD-L1 625nm',fp='LED_SMD:LED_Cree-XP',field=(414.02,312.42),mpn='XPEBRD-L1-0000-00501');route(re,2,p('D1',2))
place('Q1',('Transistor_FET','AO3400A'),403.86,337.82,value='AO3400A',field=(414.02,332.74));route('D1',1,p('Q1',3));route('Q1',2,(406.4,363.22));gnd(406.4,363.22)
rg=R('100R',398.78,353.06,90);route(rg,1,(421.64,353.06),(421.64,347.98),(393.7,347.98),(393.7,337.82),p('Q1',1));route(rg,2,(391.16,353.06));label('OPT_LED_EN',391.16,353.06,180)
rpd=R('100k',421.64,358.14);route(rpd,1,(421.64,347.98));route(rpd,2,(421.64,363.22),(406.4,363.22))
# Receiver: BPW34S reverse-biased into a 10k transimpedance stage referenced to 1.65 V, then x12 inverting AC gain.
wire((434.34,292.1),(571.5,292.1));rail('+3V3',434.34,292.1)
place('PD1',('Sensor_Optical','BPW34'),441.96,320.04,270,'BPW34S',fp='OptoDevice:Osram_BPW34S-SMD',field=(444.5,325.12),mpn='BPW34S')
route('PD1',1,(441.96,292.1));route('PD1',2,(472.44,322.58))
place('U8',('Amplifier_Operational','TLV9062xD'),480.06,320.04,value='TLV9062IDR',fp='Package_SO:SOIC-8_3.9x4.9mm_P1.27mm',field=(477.52,330.2),mpn='TLV9062IDR',unit=1)
wire((472.44,317.5),(459.74,317.5));label('OPT_VREF',459.74,317.5)
rf=R('10k',480.06,299.72,90);wire(p('U8',2),(467.36,322.58),(467.36,299.72),p(rf,1));wire(p(rf,2),(492.76,299.72),(492.76,320.04),p('U8',1))
cfb=C('10p C0G',480.06,307.34,90);wire((467.36,307.34),p(cfb,1));wire(p(cfb,2),(492.76,307.34))
# Inverting gain stage: baseline sits at VREF, received pulses swing down toward 0.45 V.
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cac=C('10n',502.92,340.36,90);rg1=R('10k',510.54,340.36,90)
wire(p(rg1,2),(516.89,340.36),(516.89,335.28))
place('U8',('Amplifier_Operational','TLV9062xD'),525.78,332.74,value='TLV9062IDR',fp='Package_SO:SOIC-8_3.9x4.9mm_P1.27mm',field=(523.24,342.9),mpn='TLV9062IDR',unit=2)
wire((516.89,335.28),p('U8',6));wire(p('U8',5),(505.46,330.2));label('OPT_VREF',505.46,330.2)
rg2=R('120k',527.05,347.98,90);route('U8',7,(538.48,332.74),(538.48,347.98),p(rg2,2));wire(p(rg2,1),(516.89,347.98),(516.89,340.36))
wire((538.48,332.74),(543.56,332.74));label('OPT_AMP',543.56,332.74)
# 1.65 V reference and op amp supply.
rb1=R('10k',548.64,302.26);rb2=R('10k',548.64,317.5)
route(rb1,1,(548.64,292.1));route(rb1,2,(548.64,309.88),p(rb2,1));route(rb2,2,(548.64,325.12));gnd(548.64,325.12)
wire((548.64,309.88),(541.02,309.88));caprail('100n',541.02,317.5,309.88,325.12);gnd(541.02,325.12);label('OPT_VREF',548.64,309.88)
place('U8',('Amplifier_Operational','TLV9062xD'),563.88,330.2,value='TLV9062IDR',fp='Package_SO:SOIC-8_3.9x4.9mm_P1.27mm',field=(569.0,326.39),mpn='TLV9062IDR',unit=3)
route('U8',8,(563.88,292.1));route('U8',4,(563.88,363.22));gnd(563.88,363.22)
cv=caprail('100n',571.5,304.8,292.1,312.42);gnd(571.5,312.42)
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# Detection row: comparator -> AND with the emitter pulse (synchronous) -> retriggerable monostable.
wire((198.12,406.4),(568.96,406.4));rail('+3V3',198.12,406.4)
place('U4','TS3021IYLT',254,431.8,field=(255.27,414.02))
wire((238.76,434.34),p('U4',4));label('OPT_AMP',238.76,434.34,180)
rth1=R('22k',233.68,416.56);rth2=R('10k',223.52,429.26,90)
route(rth1,1,(233.68,406.4));route(rth1,2,(233.68,429.26),p('U4',3));wire(p(rth2,2),(233.68,429.26));route(rth2,1,(219.71,429.26),(219.71,444.5));gnd(219.71,444.5)
rhys=R('470k',256.54,452.12,90);route('U4',1,(266.7,431.8));wire((266.7,431.8),(266.7,452.12),p(rhys,2));wire(p(rhys,1),(236.22,452.12),(236.22,429.26))
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caprail('100n',274.32,416.56,406.4,424.18);gnd(274.32,424.18)
place('U9',('74xGxx','74LVC1G08'),299.72,431.8,value='SN74LVC1G08DBVR',fp='Package_TO_SOT_SMD:SOT-23-5',field=(299.72,411.48),mpn='SN74LVC1G08DBVR')
wire((266.7,431.8),(276.86,431.8),(276.86,429.26),p('U9',1))
rdly=R('1k',218.44,457.2,90);wire((203.2,457.2),p(rdly,1));label('OPT_LED_EN',203.2,457.2)
cdly=C('470p C0G',228.6,464.82);route(rdly,2,(228.6,457.2),p(cdly,1));route(cdly,2,(228.6,472.44));gnd(228.6,472.44)
wire((228.6,457.2),(279.4,457.2),(279.4,434.34),p('U9',2))
route('U9',5,(299.72,406.4));route('U9',3,(299.72,444.5));gnd(299.72,444.5)
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route('U10',4,(355.6,449.58));gnd(355.6,449.58)
rext=R('100k',381.0,421.64);route(rext,1,(381.0,414.02),(355.6,414.02));route(rext,2,(381.0,434.34));route('U10',7,(381.0,434.34))
cext=C('1n C0G',388.62,436.88);wire((381.0,434.34),(388.62,434.34),p(cext,1));route('U10',6,(388.62,439.42),p(cext,2))
route('U10',5,(398.78,426.72));label('OPT_TACH',398.78,426.72)
tp('TP9','TP_OPT_TACH',393.7,421.64,(393.7,426.72))
caprail('100n',365.76,416.56,406.4,424.18);gnd(365.76,424.18)
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
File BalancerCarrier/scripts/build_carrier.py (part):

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WHAT CAME WITH IT
    The reverse-polarity switch from BalancerREF Rev G. The FireBeetle's cell connector
    goes straight to its charger with no protection, and a reversed 1S pack is about 4 V
    past the absolute maximum of any charger's BAT pin. Two P-FETs source-to-source with
    the gates held at their own source, switched by an N-FET whose gate is driven from
    the cell's own positive terminal, so it is off unless the pack is the right way
    round. J1 takes the cell; J2 feeds the FireBeetle's PH2.0 by a short cable.
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
PIN MAP (FireBeetle silkscreen -> ESP32-S3 GPIO -> signal)
    Deep-sleep wake uses EXT1, which needs RTC-capable pins: GPIO0-21 on the S3. Both
    MAG_TACH and ACQUIRE are inside that range. GPIO0 and GPIO3 are strapping pins and
    are left free; GPIO43/44 are UART0 and are left free so ROM boot chatter never
    reaches the GPS, which is the same reason BalancerREF used UART1.

        SCK   GPIO17  ACCEL_SCK        D10  GPIO14  OPT_LED_EN
        MOSI  GPIO15  ACCEL_MOSI       D11  GPIO13  ACQUIRE_BUTTON   (RTC, EXT1)
        MISO  GPIO16  ACCEL_MISO       D12  GPIO12  OPT_TACH
        A4/SS GPIO10  ACCEL_CS         D13  GPIO21  STATUS_LED
        D5    GPIO7   ACCEL_DRDY       A0   GPIO4   GPS_UART_TX
        D6    GPIO18  MAG_TACH  (RTC)  A1   GPIO5   GPS_UART_RX
                                       A2   GPIO6   SUPPLY_SENSE

    Free after this: D2(3) D3(38) D7(9) D9(0) D14(47) A3(8) A5(11) SDA(1) SCL(2)
    TX(43) RX(44) - eleven spare.
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]
# which FireBeetle pin each carrier signal lands on
# Keyed by GPIO name so each choice can be checked against the ESP32-S3 datasheet.
#   ACQUIRE_BUTTON must be an RTC GPIO (0-21) to wake the part from deep sleep on EXT1.
#   SUPPLY_SENSE must be on ADC1 (GPIO1-10); ADC2 is unusable while Wi-Fi is up.
#   IO0 carries the board's own K3 boot button, IO43/IO44 are the UART0 console, and
#   IO3 is a strapping pin - all three are left alone.
NET_ON_GPIO = {
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              if nam in NET_ON_GPIO}
assert len(NET_ON_PIN) == len(NET_ON_GPIO), 'a GPIO in NET_ON_GPIO is not on a header'
_g = {s: int(n[2:]) for n, s in NET_ON_GPIO.items()}
assert 0 <= _g['ACQUIRE_BUTTON'] <= 21, 'ACQUIRE_BUTTON is not an RTC GPIO - cannot wake deep sleep'
assert 1 <= _g['SUPPLY_SENSE'] <= 10, 'SUPPLY_SENSE is not on ADC1 - ADC2 is dead while Wi-Fi runs'

used, custom, instances, pins_of, wires, labels, ncs = {}, {}, [], {}, [], [], []
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# The cell plugs straight into the FireBeetle's own J1. Nothing here.
#
# DFR0975-U schematic V1.3 sheet 1 shows Q2 (AO3400, N-channel) sitting in the
# battery's LOW side between the connector's negative pin and BAT-, with its gate
# taken from VBAT+. That is reverse-polarity protection, and a better arrangement
# than the discrete P-FET pair this carrier used to carry: one FET instead of three,
# in the return path so no gate-drive network is needed, and no standing drain on
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
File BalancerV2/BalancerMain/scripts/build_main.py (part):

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# ================================================================ Feather
# Signals by Feather position. GPIO on the two boards (FeatherS3 pinout card; Adafruit
# arduino-esp32 variant adafruit_feather_esp32s3):
#   A0 MAG_TACH   FeatherS3 IO17, Adafruit GPIO18   (RTC GPIO on both: can wake the chip)
#   A1 OPT_TACH   IO18 / GPIO17                     A2 ACQUIRE_BUTTON IO14 / GPIO16 (RTC)
#   A3 STATUS_LED IO12 / GPIO15                     A4 BOOST_EN       IO6  / GPIO14
#   A5 ACCEL_INT  IO5  / GPIO8                      SDA/SCL           IO8/IO9 / GPIO3/GPIO4
# AREF (FeatherS3 IO0, a strapping pin) and the 16th pin (FeatherS3 LDO2 output) stay open.
GPIO = {'A0': 'MAG_TACH', 'A1': 'OPT_TACH', 'A2': 'ACQUIRE_BUTTON', 'A3': 'STATUS_LED', 'A4': 'BOOST_EN',
        'A5': 'ACCEL_INT', 'SDA': 'ACCEL_SDA', 'SCL': 'ACCEL_SCL'}
FX, FY = 254.0, 101.6
fb = place('U1', 'BalancerMain:Feather', 'Feather ESP32-S3', FX, FY, 0, 'BalancerMain:Feather_Socket')
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two('C10', C, '100n', 182.88, 266.7, 0, FP_C, '+3V3', 'GND')         # LM1815 decoupling

# ================================================================ Banner photo-tach
# M12: pin 1 brown +12 V, pin 3 blue 0 V, pin 2 white NPN output. White pulls OPT_RAW low.
j2 = place('J2', 'BalancerMain:Conn_01x03', 'BANNER bn/bu/wh', 25.4, 322.58, 0, 'BalancerMain:SolderWire_1x03')
connect(j2, {'1': '+12V', '2': 'GND', '3': 'OPT_RAW'})
two('R14', R, '10k', 63.5, 309.88, 0, FP_R, '+3V3', 'OPT_RAW')
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
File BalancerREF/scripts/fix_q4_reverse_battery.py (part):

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add_w += [wire(Q4_S, Q5_S), wire(SRC_TAP, SRC_LBL),
          wire(Q4_D, CELL_LBL), wire(Q5_D, BAT_LBL),
          wire(Q4_G, G4_LBL), wire(Q5_G, G5_LBL)]
add_l += [label('BPS_SRC', *SRC_LBL, 180), label('BAT_CELL', *CELL_LBL, 90),
          label('BAT', *BAT_LBL, 270), label('BPS_GATE', *G4_LBL, 180),
          label('BPS_GATE', *G5_LBL)]
add_j = [junction(*SRC_TAP)]

# ---- the control network ---------------------------------------------------
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    wire(R43_R, Q6_G), wire(R43_L, R43_LBL),
    wire(Q6_S, Q6_GND),
]
add_l += [label('BPS_SRC', *SRC_BUS[0], 180), label('BPS_GATE', *GATE_BUS[0], 180),
          label('BAT_CELL', *R43_LBL, 180)]
add_j += [junction(281.94, 170.18), junction(289.56, 170.18), junction(*Q6_G)]

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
